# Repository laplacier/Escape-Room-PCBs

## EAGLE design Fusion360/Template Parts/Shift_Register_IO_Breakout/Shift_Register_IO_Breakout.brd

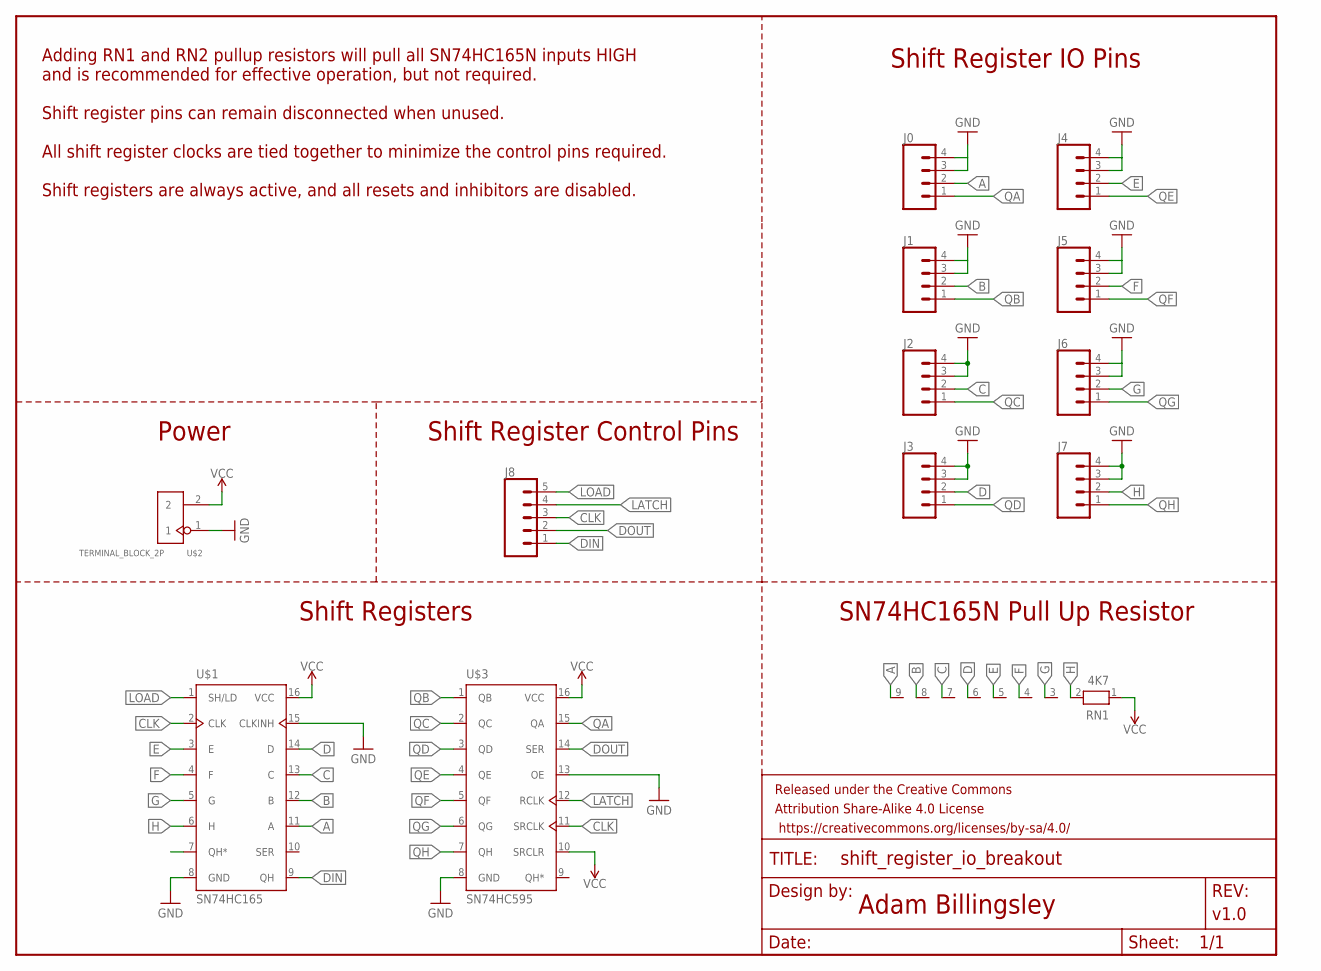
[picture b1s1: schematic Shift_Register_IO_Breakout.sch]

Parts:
FRAME1: FRAME-LETTER; CREATIVE_COMMONS
J0, J1, J2, J3, J4, J5, J6, J7: CONN_04; 1X04
J8: CONN_05; 1X05
RN1: 4K7; RN-9
U$1: SN74HC165; DIL16
U$2: TERMINAL_BLOCK_2P; H2-5.0-10.5X8.0MM
U$3: SN74HC595; DIL16

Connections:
A: J0.2, RN1.9, U$1.11 (A)
B: J1.2, RN1.8, U$1.12 (B)
C: J2.2, RN1.7, U$1.13 (C)
CLK: J8.3, U$1.2 (CLK), U$3.11 (SRCLK)
D: J3.2, RN1.6, U$1.14 (D)
DIN: J8.1, U$1.9 (QH)
DOUT: J8.2, U$3.14 (SER)
E: J4.2, RN1.5, U$1.3 (E)
F: J5.2, RN1.4, U$1.4 (F)
G: J6.2, RN1.3, U$1.5 (G)
GND: J0.3, J0.4, J1.3, J1.4, J2.3, J2.4, J3.3, J3.4, J4.3, J4.4, J5.3, J5.4, J6.3, J6.4, J7.3, J7.4, U$1.8 (GND), U$1.15 (CLKINH), U$2.1, U$3.8 (GND), U$3.13 (OE)
H: J7.2, RN1.2, U$1.6 (H)
LATCH: J8.4, U$3.12 (RCLK)
LOAD: J8.5, U$1.1 (SH/LD)
QA: J0.1, U$3.15 (QA)
QB: J1.1, U$3.1 (QB)
QC: J2.1, U$3.2 (QC)
QD: J3.1, U$3.3 (QD)
QE: J4.1, U$3.4 (QE)
QF: J5.1, U$3.5 (QF)
QG: J6.1, U$3.6 (QG)
QH: J7.1, U$3.7 (QH)
VCC: RN1.1, U$1.16 (VCC), U$2.2, U$3.10 (SRCLR), U$3.16 (VCC)

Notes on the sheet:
Adding RN1 and RN2 pullup resistors will pull all SN74HC165N inputs HIGH and is recommended for effective operation, but not required.
Shift register pins can remain disconnected when unused.
All shift register clocks are tied together to minimize the control pins required.
Shift registers are always active, and all resets and inhibitors are disabled.
Shift Registers
SN74HC165N Pull Up Resistor
Shift Register IO Pins
Shift Register Control Pins
Power

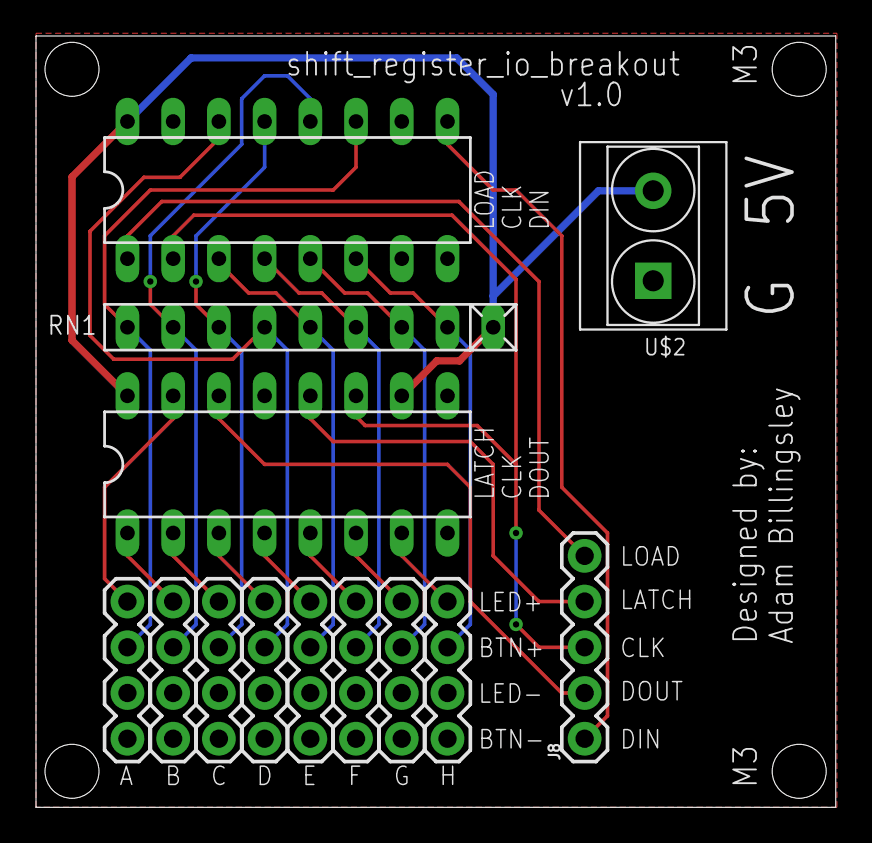
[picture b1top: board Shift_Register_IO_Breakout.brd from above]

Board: 2 copper layers, 44.4 x 42.9 mm, 14 parts (0 on the bottom side), 23 nets.

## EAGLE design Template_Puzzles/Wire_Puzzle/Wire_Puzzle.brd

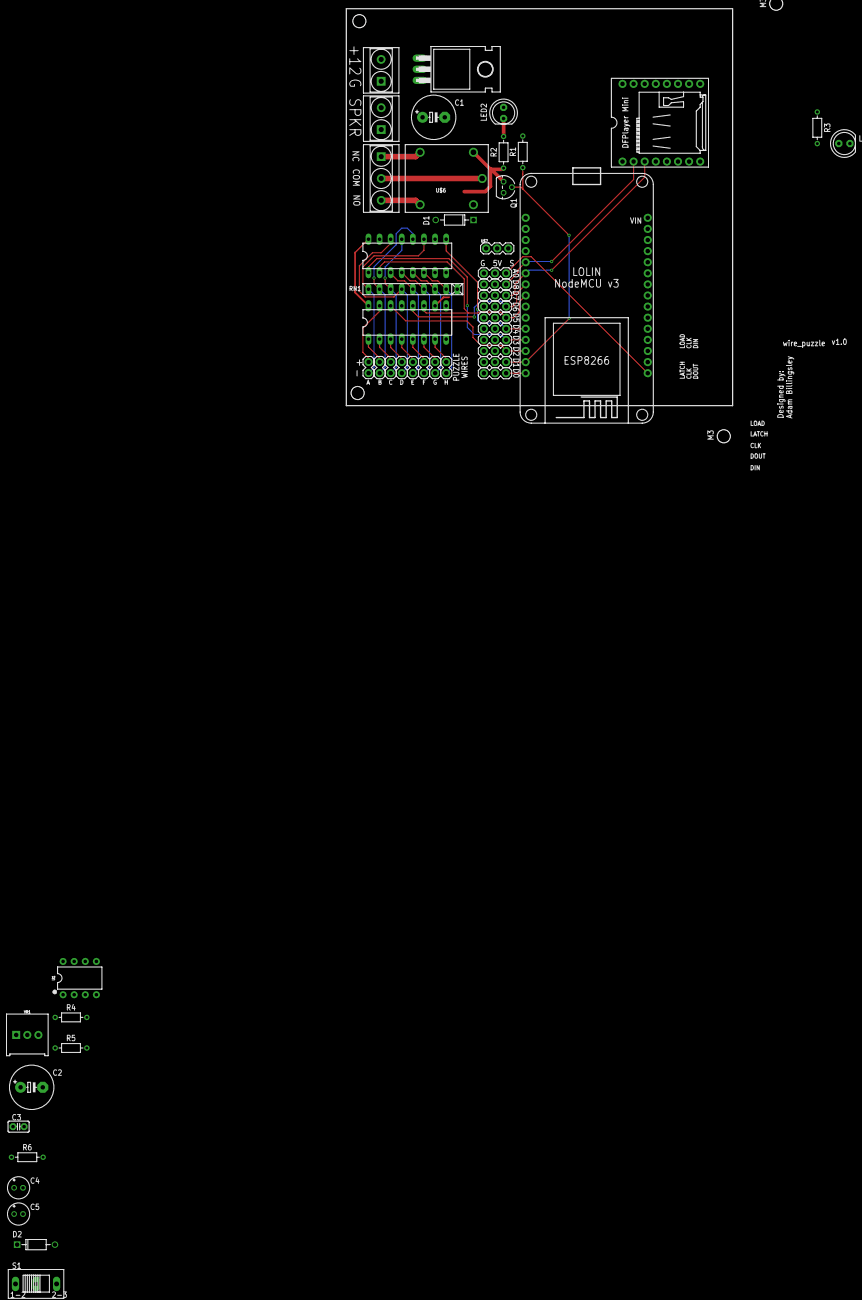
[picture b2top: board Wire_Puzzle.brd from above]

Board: 2 copper layers, 88.4 x 90.8 mm, 49 parts (0 on the bottom side), 44 nets.

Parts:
C1: 1000uF; E5-10,5
C2: 100uF; E5-10,5
C3: 0.1uF; C2.5-2
C4: 0.33uF; E2-5
C5: 0.1uF; E2-5
D1, D2: 1N4001; DO-41
FRAME1: FRAME-LEDGER; CREATIVE_COMMONS
IC1: 7805T; TO220H
LED1, LED2: LED5MM
Q1: 2N7000; TO92
R1, R4, R5: 1K; RESAD724W46L381D178B
R2, R3: 330R; RESAD724W46L381D178B
R6: 10R; RESAD724W46L381D178B
RN1: 4K7; RN-9
S1: SWITCH_SLIDING_SSP1S1
U1: LM386N; DIP08
U$1: SN74HC165; DIL16
U$2, U$9: TERMINAL_BLOCK_2P; H2-5.0-10.5X8.0MM
U$3: SN74HC595; DIL16
U$4: LOLIN_NODEMCU
U$5: DFPLAYER_MINI; DFMINI
U$6: RELAY-5PIN; RELAY-19.0X15.0X15.0MM
U$7, U$18, U$19, U$20, U$21, U$22, U$23, U$24, U$25, U$26, U$27: 1X03
U$8: TERMINAL_BLOCK_3P; H3-5.0-15.5X8.0MM
U$10, U$11, U$12, U$13, U$14, U$15, U$16, U$17: 1X02
VR1: 10k; TRIMPOT-PTH-3386U

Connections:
5V: C5.+, D1.C, D2.A, IC1.3, LED2.A, R3.1, U$1.16, U$3.10, U$3.16, U$4.P$1, U$5.P$9, U$6.3, U$7.3, U$18.2, U$19.2, U$20.2, U$21.2, U$22.2, U$23.2, U$24.2, U$25.2, U$26.2, U$27.2
A: RN1.9, U$1.11, U$10.2
A0: U$4.P$15, U$27.3
AUDIO: R4.1, R5.1, VR1.2
B: RN1.8, U$1.12, U$11.2
C: RN1.7, U$1.13, U$12.2
D: RN1.6, U$1.14, U$13.2
D0: U$4.P$31, U$7.2, U$18.3
D1: Q1.2, R1.1, U$4.P$30, U$19.3
D2: U$3.14, U$4.P$29, U$20.3
D3: U$1.1, U$4.P$28, U$21.3
D4: U$1.9, U$4.P$27, U$22.3
D5: U$1.2, U$3.11, U$4.P$24, U$23.3
D6: U$3.12, U$4.P$23, U$24.3
D7: U$4.P$22, U$5.P$11, U$25.3
D8: U$4.P$21, U$5.P$10, U$26.3
E: RN1.5, U$1.3, U$14.2
F: RN1.4, U$1.4, U$15.2
G: RN1.3, U$1.5, U$16.2
GND: C2.-, C4.-, C5.-, IC1.2, LED1.K, Q1.3, R1.2, R6.2, RN1.1, U1.2, U1.4, U$1.8, U$1.15, U$2.1, U$3.8, U$3.13, U$4.P$2, U$4.P$14, U$4.P$25, U$5.P$7, U$5.P$15, U$7.1, U$9.2, U$18.1, U$19.1, U$20.1, U$21.1, U$22.1, U$23.1, U$24.1, U$25.1, U$26.1, U$27.1
H: RN1.2, U$1.6, U$17.2
unnamed: U$6.1, U$8.2
unnamed: U$6.4, U$8.1
unnamed: U$6.5, U$8.3
unnamed: D1.A, Q1.1, R2.1, U$6.2
unnamed: LED1.A, R3.2
unnamed: LED2.K, R2.2
unnamed: C1.+, C3.1, U1.5
unnamed: R4.2, U$5.P$12
unnamed: C1.-, U$9.1
unnamed: C3.2, R6.1
unnamed: R5.2, U$5.P$13
unnamed: U1.3, VR1.3
unnamed: S1.2, U$2.2
unnamed: C2.+, U1.7
QA: U$3.15, U$10.1
QB: U$3.1, U$11.1
QC: U$3.2, U$12.1
QD: U$3.3, U$13.1
QE: U$3.4, U$14.1
QF: U$3.5, U$15.1
QG: U$3.6, U$16.1
QH: U$3.7, U$17.1
VCC: C4.+, D2.C, IC1.1, S1.3, U1.6

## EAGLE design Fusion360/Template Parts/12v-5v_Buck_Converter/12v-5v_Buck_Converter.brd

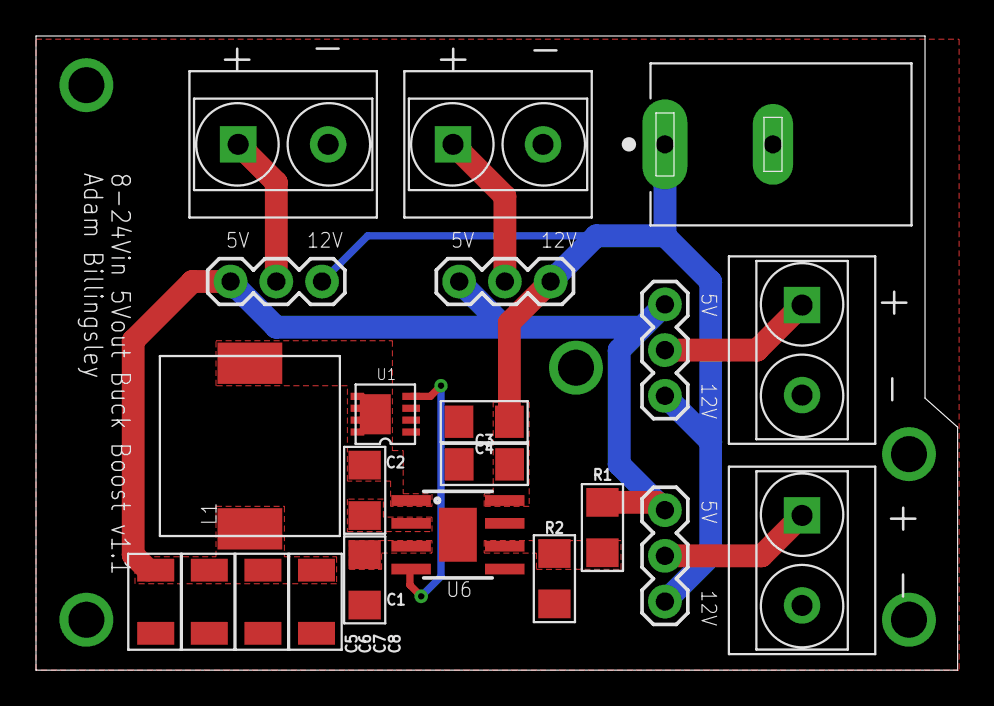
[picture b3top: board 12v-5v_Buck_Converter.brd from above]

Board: 2 copper layers, 51.2 x 35.2 mm, 23 parts (1 on the bottom side), 12 nets.

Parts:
C1, C2: 1uF; 1206-CAPACITOR
C3, C4: 10uF; 1206-CAPACITOR
C5, C6, C7, C8: 22uF; 1210
FRAME1: FRAME-LETTER; CREATIVE_COMMONS
J1: PJ-037A; CUI_PJ-037A
JP1, JP2, JP3, JP4: 1X03
L1: 4.7uH; INDUCTOR-7443330470
R1: 93.1k; 1206-CAPACITOR
R2: 18k; 1206-CAPACITOR
U1: ZXMN3A01Z; SI7114DN
U2, U3, U4, U5: TERMINAL_BLOCK_2P; H2-5.0-10.5X8.0MM
U6: RT7258GSP; SOP-8E

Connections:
5V: C5.1, C6.1, C7.1, C8.1, JP1.3, JP2.3, JP3.3, JP4.3, L1.2, R1.2
12V: C3.1, C4.1, J1.1, JP1.1, JP2.1, JP3.1, JP4.1, U6.8
BG: U1.4, U6.4
BOOT: C2.1, U6.2
FB: R1.1, R2.2, U6.6
GND: C1.2, C3.2, C4.2, C5.2, C6.2, C7.2, C8.2, J1.2, R2.1, U1.1, U1.2, U1.3, U2.2, U3.2, U4.2, U5.2, U6.5, U6.9
unnamed: C1.1, U6.3
unnamed: JP4.2, U5.1
unnamed: JP3.2, U4.1
unnamed: JP2.2, U3.1
unnamed: JP1.2, U2.1
SW: C2.2, L1.1, U1.5, U1.6, U1.7, U1.8, U1.9, U6.1

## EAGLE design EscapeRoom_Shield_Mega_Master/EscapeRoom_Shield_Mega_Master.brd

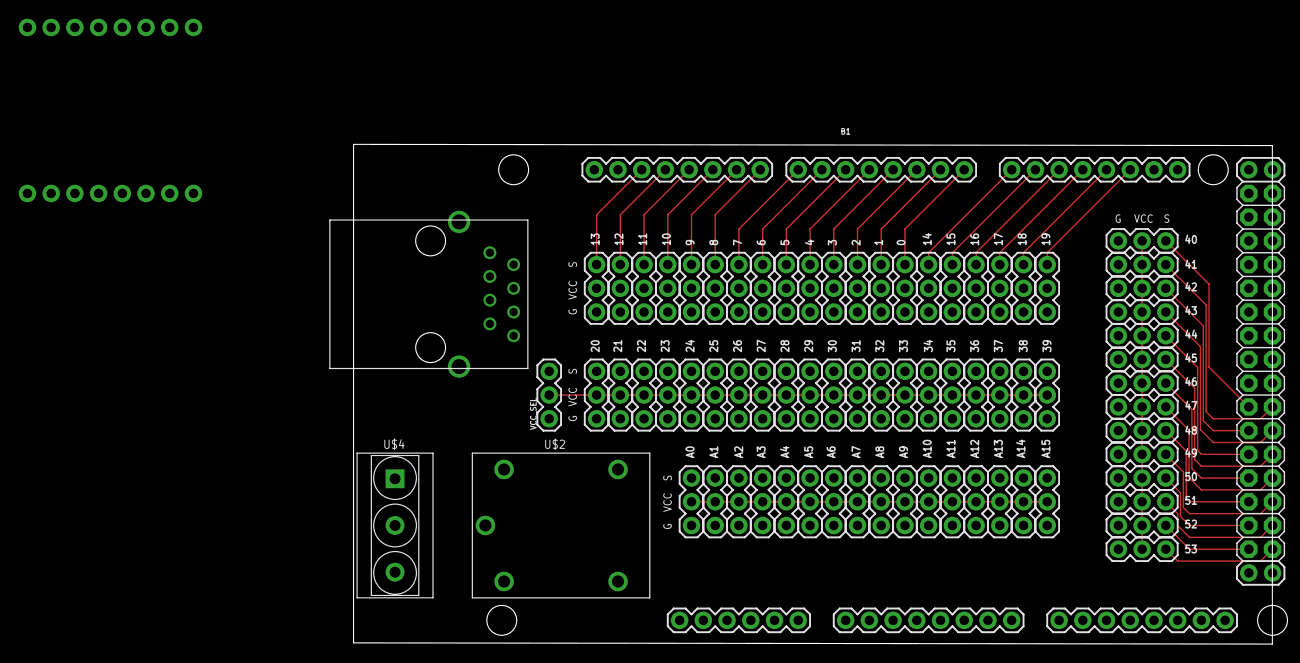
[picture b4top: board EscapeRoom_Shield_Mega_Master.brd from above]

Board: 2 copper layers, 98.4 x 53.5 mm, 76 parts (0 on the bottom side), 74 nets.

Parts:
0, 1, 2, 3, 4, 5, 6, 7, 8, 9, 10, 11, 12, 13, 14, 15, 16, 17, 18, 19, 20, 21, 22, 23, 24, 25, 26, 27, 28, 29, 30, 31, 32, 33, 34, 35, 36, 37, 38, 39, 40, 41, 42, 43, 44, 45, 46, 47, 48, 49, 50, 51, 52, 53: 1X03
A0, A1, A2, A3, A4, A5, A6, A7, A8, A9, A10, A11, A12, A13, A14, A15: 1X03
B1: ARDUINO_MEGA_R3FULL; ARDUINO_MEGA
U$1: ETHERNET_MTJ-88GX1-FSD-PG6; RJ45_MTJ-88GX1-FSD-PG6
U$2: RELAY-AZ943-1CH-5DE; RELAY-19.0X15.0X15.0MM
U$3: DFPLAYER_MINI; DFMINI
U$4: TERMINAL_BLOCK_3P; H3-5.0-15.5X8.0MM
VCC_SEL: 1X03

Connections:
0: 0.3, B1.0
1: 1.3, B1.1
2: 2.3, B1.2
3: 3.3, B1.3
3.3V: B1.3.3V, VCC_SEL.1
4: 4.3, B1.4
5: 5.3, B1.5
5V: B1.5V@0, B1.5V@1, B1.5V@2, VCC_SEL.3
6: 6.3, B1.6
7: 7.3, B1.7
8: 8.3, B1.8
9: 9.3, B1.9
10: 10.3, B1.10
11: 11.3, B1.11
12: 12.3, B1.12
13: 13.3, B1.13
14: 14.3, B1.14
15: 15.3, B1.15
16: 16.3, B1.16
17: 17.3, B1.17
18: 18.3, B1.18
19: 19.3, B1.19
20: 20.3, B1.20
21: 21.3, B1.21
22: 22.3, B1.22
23: 23.3, B1.23
24: 24.3, B1.24
25: 25.3, B1.25
26: 26.3, B1.26
27: 27.3, B1.27
28: 28.3, B1.28
29: 29.3, B1.29
30: 30.3, B1.30
31: 31.3, B1.31
32: 32.3, B1.32
33: 33.3, B1.33
34: 34.3, B1.34
35: 35.3, B1.35
36: 36.3, B1.36
37: 37.3, B1.37
38: 38.3, B1.38
39: 39.3, B1.39
40: 40.3, B1.40
41: 41.3, B1.41
42: 42.3, B1.42
43: 43.3, B1.43
44: 44.3, B1.44
45: 45.3, B1.45
46: 46.3, B1.46
47: 47.3, B1.47
48: 48.3, B1.48
49: 49.3, B1.49
50: 50.3, B1.50
51: 51.3, B1.51
52: 52.3, B1.52
53: 53.3, B1.53
A0: A0.3, B1.A0
A1: A1.3, B1.A1
A2: A2.3, B1.A2
A3: A3.3, B1.A3
A4: A4.3, B1.A4
A5: A5.3, B1.A5
A6: A6.3, B1.A6
A7: A7.3, B1.A7
A8: A8.3, B1.A8
A9: A9.3, B1.A9
A10: A10.3, B1.A10
A11: A11.3, B1.A11
A12: A12.3, B1.A12
A13: A13.3, B1.A13
A14: A14.3, B1.A14
A15: A15.3, B1.A15
GND: 0.1, 1.1, 2.1, 3.1, 4.1, 5.1, 6.1, 7.1, 8.1, 9.1, 10.1, 11.1, 12.1, 13.1, 14.1, 15.1, 16.1, 17.1, 18.1, 19.1, 20.1, 21.1, 22.1, 23.1, 24.1, 25.1, 26.1, 27.1, 28.1, 29.1, 30.1, 31.1, 32.1, 33.1, 34.1, 35.1, 36.1, 37.1, 38.1, 39.1, 40.1, 41.1, 42.1, 43.1, 44.1, 45.1, 46.1, 47.1, 48.1, 49.1, 50.1, 51.1, 52.1, 53.1, A0.1, A1.1, A2.1, A3.1, A4.1, A5.1, A6.1, A7.1, A8.1, A9.1, A10.1, A11.1, A12.1, A13.1, A14.1, A15.1, B1.GND@0, B1.GND@1, B1.GND@2, B1.GND@3, B1.GND@4
VCC: 0.2, 1.2, 2.2, 3.2, 4.2, 5.2, 6.2, 7.2, 8.2, 9.2, 10.2, 11.2, 12.2, 13.2, 14.2, 15.2, 16.2, 17.2, 18.2, 19.2, 20.2, 21.2, 22.2, 23.2, 24.2, 25.2, 26.2, 27.2, 28.2, 29.2, 30.2, 31.2, 32.2, 33.2, 34.2, 35.2, 36.2, 37.2, 38.2, 39.2, 40.2, 41.2, 42.2, 43.2, 44.2, 45.2, 46.2, 47.2, 48.2, 49.2, 50.2, 51.2, 52.2, 53.2, A0.2, A1.2, A2.2, A3.2, A4.2, A5.2, A6.2, A7.2, A8.2, A9.2, A10.2, A11.2, A12.2, A13.2, A14.2, A15.2, VCC_SEL.2

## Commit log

2022-10-06 Initial Commit
    Brainstorming additions. Added RJ45 for I2C and a relay for puzzle solution. Need to add DFMini Player, speakers, and voltage converter.
2022-10-06 Added all GPIO headers
    Placement seems good, but no space for the DFMini on the current layout. Board will have to exceed the footprint of the Mega, but need more additions to justify the space increase.
2022-10-18 Finished defining pin breakouts, wiring pins
2022-11-11 Changed DFMini TX/RX pins to compatible pins. Removed R1. Labeled 12V out terminal blocks.
2022-11-14 Added Buck Boost circuit
2022-12-01 Redesign to fix incorrect specs
    MOSFET needed to have a Vgs of 5V and all of the other passive components were adjusted to be more temperature/current compatible
2023-02-13 updated buck converter, added shift register boards
2023-02-13 Added pdf schematics to shift register boards
2023-02-14 Wire_Puzzle progress
2023-02-14 Progress, added audio amp, power
2023-02-15 Finished wire puzzle
2023-02-15 Cleaned up Wire_Puzzle PCB labels, added DC power jack
2023-04-26 Reorganized, started prop_template
    Trying to transition from EAGLE to KiCad for monetary purposes. Sorted schematics into program specific folders and began prop_template in KiCad.
2023-10-15 exported gerbers

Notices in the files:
parts and their libraries:
SparkFun-Aesthetics: Licensing: Creative Commons ShareAlike 4.0 International - https://creativecommons.org/licenses/by-sa/4.0
SparkFun-Aesthetics: Released under the Creative Commons Attribution Share-Alike 4.0 License
SparkFun-Aesthetics: https://creativecommons.org/licenses/by-sa/4.0
